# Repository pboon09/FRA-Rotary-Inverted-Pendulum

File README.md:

# FRA421 Embedded Systems Final Project

## Overview

Advanced embedded system implementation with state estimation filters, multiple interfaces, and safety-critical design for Rotary Inverted Pendulum control.

## Features

### State Estimation
- ✅ **Kalman Filter** - Optimal velocity estimation from encoder positions
- ✅ **Low-Pass Filter** - Noise reduction
- ✅ **CMSIS DSP Library** - Optimized signal processing

### Multi-Interface System
- ✅ **Colors Shield LED (8×8)** - End-effector position visualization
- ✅ **LCD Display** - Real-time joint position and velocity display
- ✅ **SD Card Logging** - Position/velocity data logging
- ✅ **Bluetooth (HC-05)** - Wireless command interface

### Safety & Efficiency
- ✅ **Safety-critical programming** - Fault detection, graceful degradation
- ✅ **Low Power Modes** - Sleep modes during idle periods
- ✅ **Watchdog Timer** - System reliability

### Hardware Integration
- ✅ **Custom PCB** - All interfaces integrated on single board
- ✅ **Non-blocking architecture** - Concurrent interface operation

## System Architecture
```
STM32 NUCLEO-G474RE
    ├─ Encoders (AMT103-V) → Kalman Filter → LQR Controller → Motor
    ├─ LED Matrix → End-effector position (X-Y grid)
    ├─ LCD → Position and velocity display
    ├─ SD Card → CSV data logging
    └─ Bluetooth → Command reception (start/stop/config)
```

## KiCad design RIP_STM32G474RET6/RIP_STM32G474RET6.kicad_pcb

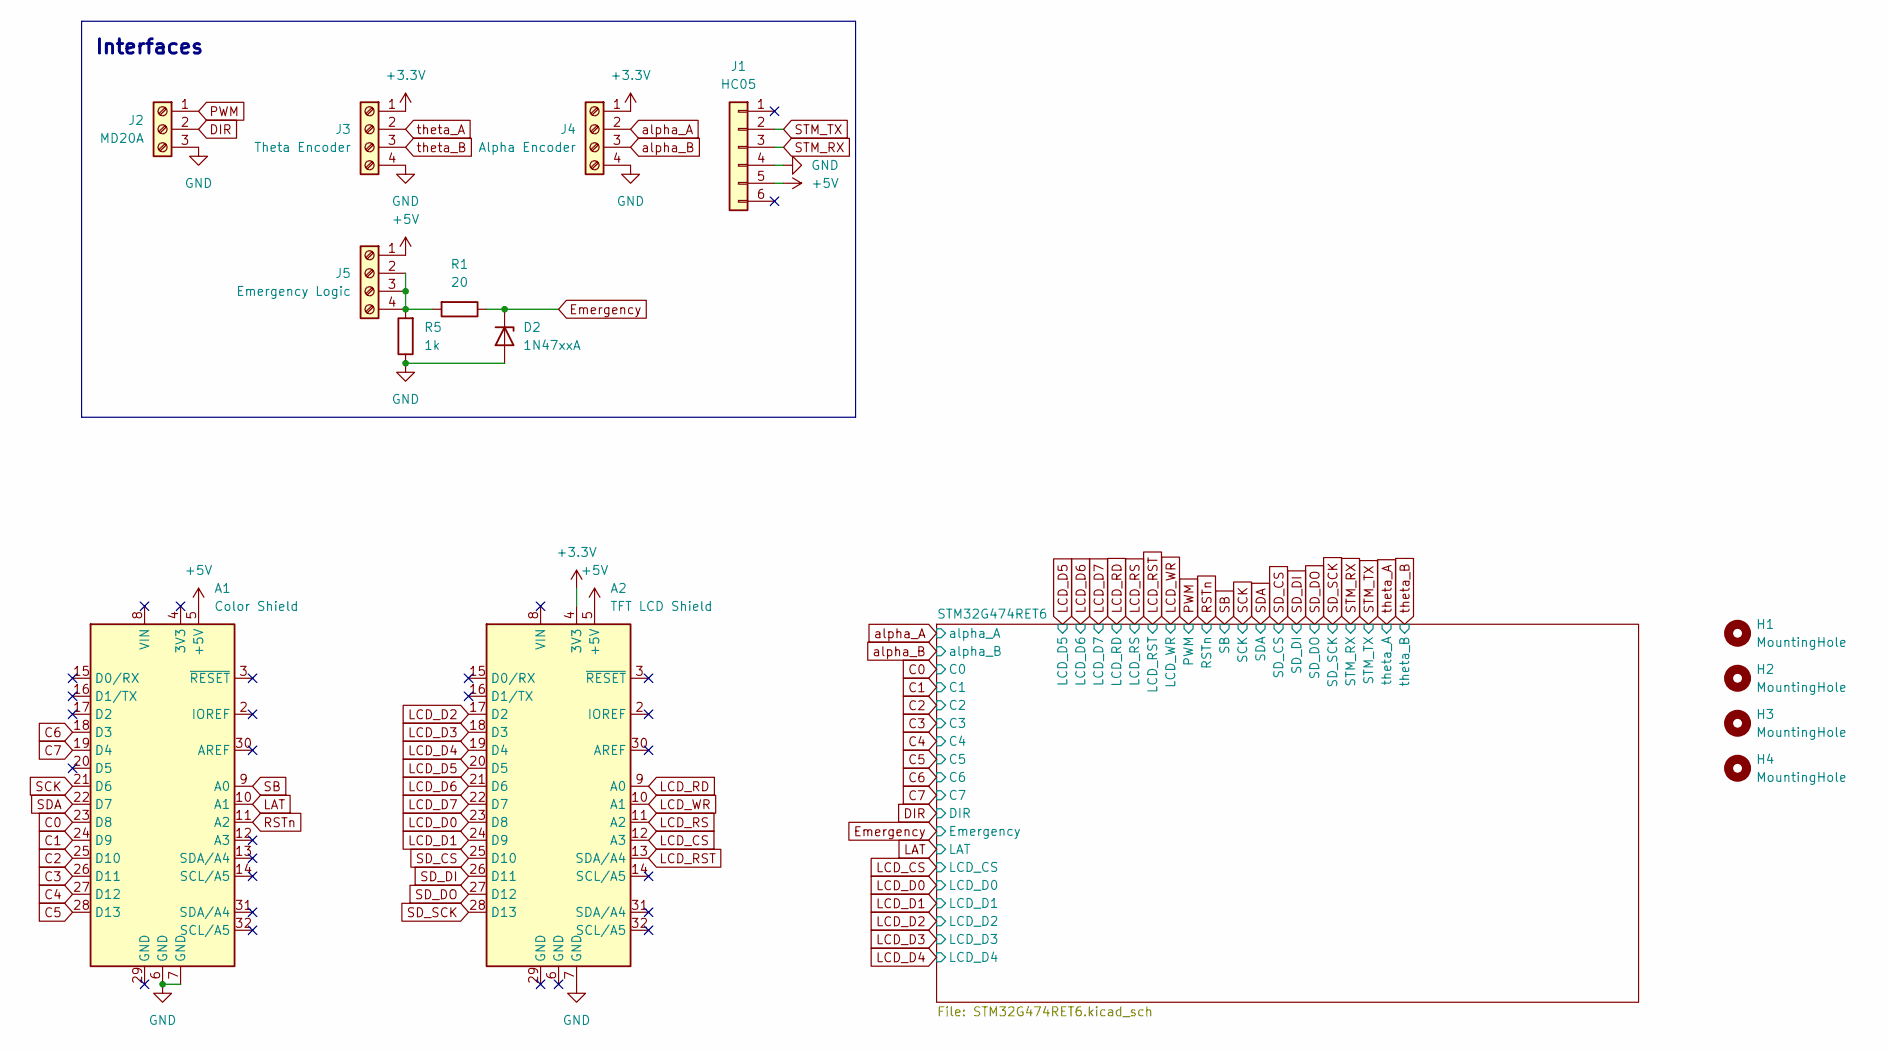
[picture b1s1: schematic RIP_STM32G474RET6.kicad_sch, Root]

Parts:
A1: Color Shield; Arduino_UNO_R3
A2: TFT LCD Shield; Arduino_UNO_R3
D2: 1N47xxA; D_DO-41_SOD81_P10.16mm_Horizontal
H1, H2, H3, H4: MountingHole; MountingHole_3mm
J1: HC05; PinSocket_1x06_P2.54mm_Vertical
J2: MD20A; PhoenixContact_MC_1,5_3-G-5.08_1x03_P5.08mm_Horizontal
J3: Theta Encoder; PhoenixContact_MC_1,5_4-G-5.08_1x04_P5.08mm_Horizontal
J4: Alpha Encoder; PhoenixContact_MC_1,5_4-G-5.08_1x04_P5.08mm_Horizontal
J5: Emergency Logic; PhoenixContact_MC_1,5_4-G-5.08_1x04_P5.08mm_Horizontal
R1: 20; R_Axial_DIN0309_L9.0mm_D3.2mm_P12.70mm_Horizontal
R5: 1k; R_Axial_DIN0309_L9.0mm_D3.2mm_P12.70mm_Horizontal

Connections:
+5V: A1.5 (+5V), A2.5 (+5V), J1.5, J5.1; also elsewhere on the board
C0: A1.23 (D8); also elsewhere on the board
C1: A1.24 (D9); also elsewhere on the board
C2: A1.25 (D10); also elsewhere on the board
C3: A1.26 (D11); also elsewhere on the board
C4: A1.27 (D12); also elsewhere on the board
C5: A1.28 (D13); also elsewhere on the board
C6: A1.18 (D3); also elsewhere on the board
C7: A1.19 (D4); also elsewhere on the board
DIR: J2.2; also elsewhere on the board
Emergency: D2.1 (K), R1.1; also elsewhere on the board
LAT: A1.10 (A1); also elsewhere on the board
LCD_CS: A2.12 (A3); also elsewhere on the board
LCD_D0: A2.23 (D8); also elsewhere on the board
LCD_D1: A2.24 (D9); also elsewhere on the board
LCD_D2: A2.17 (D2); also elsewhere on the board
LCD_D3: A2.18 (D3); also elsewhere on the board
LCD_D4: A2.19 (D4); also elsewhere on the board
LCD_D5: A2.20 (D5); also elsewhere on the board
LCD_D6: A2.21 (D6); also elsewhere on the board
LCD_D7: A2.22 (D7); also elsewhere on the board
LCD_RD: A2.9 (A0); also elsewhere on the board
LCD_RS: A2.11 (A2); also elsewhere on the board
LCD_RST: A2.13 (SDA/A4); also elsewhere on the board
LCD_WR: A2.10 (A1); also elsewhere on the board
unnamed: J5.2, J5.3, J5.4, R1.2, R5.2
PWM: J2.1; also elsewhere on the board
RSTn: A1.11 (A2); also elsewhere on the board
SB: A1.9 (A0); also elsewhere on the board
SCK: A1.21 (D6); also elsewhere on the board
SDA: A1.22 (D7); also elsewhere on the board
SD_CS: A2.25 (D10); also elsewhere on the board
SD_DI: A2.26 (D11); also elsewhere on the board
SD_DO: A2.27 (D12); also elsewhere on the board
SD_SCK: A2.28 (D13); also elsewhere on the board
STM_RX: J1.3; also elsewhere on the board
STM_TX: J1.2; also elsewhere on the board
VDD: A2.4 (3V3), J3.1, J4.1; also elsewhere on the board
VSSA: A1.6 (GND), A1.7 (GND), A2.7 (GND), D2.2 (A), J1.4, J2.3, J3.4, J4.4, R5.1; also elsewhere on the board
alpha_A: J4.2; also elsewhere on the board
alpha_B: J4.3; also elsewhere on the board
theta_A: J3.2; also elsewhere on the board
theta_B: J3.3; also elsewhere on the board

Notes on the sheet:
Interfaces

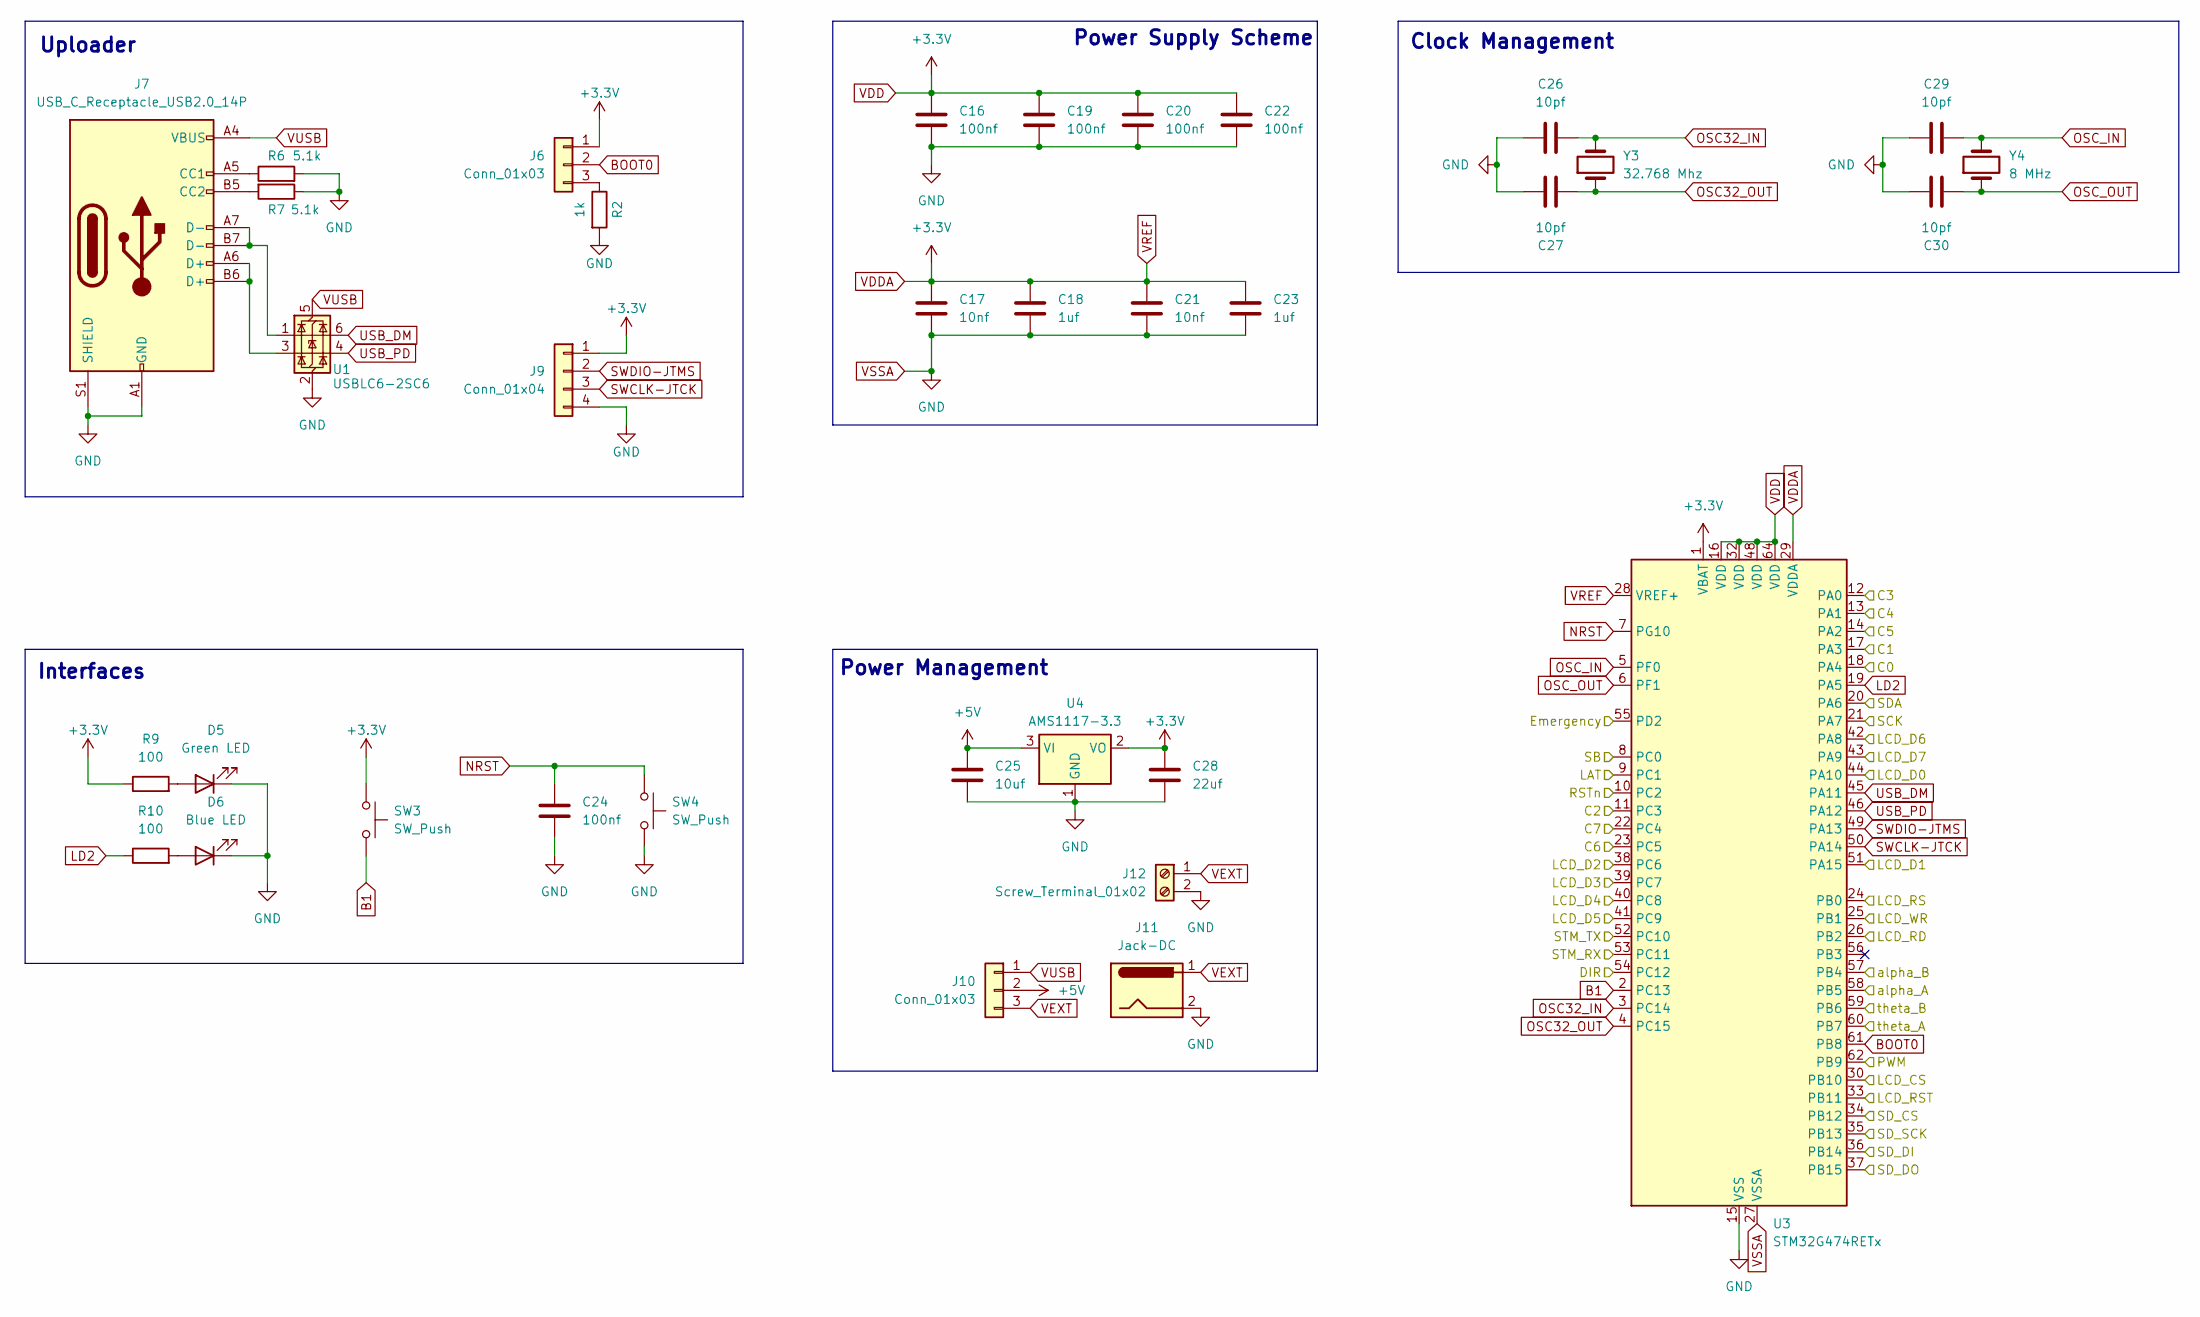
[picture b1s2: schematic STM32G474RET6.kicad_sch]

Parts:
C16, C19, C20, C22, C24: 100nf; C_0402_1005Metric
C17, C21: 10nf; C_0402_1005Metric
C18, C23: 1uf; C_0402_1005Metric
C25: 10uf; C_0402_1005Metric
C26, C27, C29, C30: 10pf; C_0402_1005Metric
C28: 22uf; C_0402_1005Metric
D5: Green LED; LED_0603_1608Metric
D6: Blue LED; LED_0603_1608Metric
J6, J10: Conn_01x03; PinHeader_1x03_P2.54mm_Vertical
J7: USB_C_Receptacle_USB2.0_14P; USB_C_Receptacle_GCT_USB4105-xx-A_16P_TopMnt_Horizontal
J9: Conn_01x04; PinHeader_1x04_P2.54mm_Vertical
J11: Jack-DC; BarrelJack_Horizontal
J12: Screw_Terminal_01x02; PhoenixContact_MC_1,5_2-G-5.08_1x02_P5.08mm_Horizontal
R2: 1k; R_0402_1005Metric
R6, R7: 5.1k; R_0402_1005Metric
R9, R10: 100; R_0402_1005Metric
SW3, SW4: SW_Push; SW_SPST_PTS810
U1: USBLC6-2SC6; SOT-23-6
U3: STM32G474RETx; LQFP-64_10x10mm_P0.5mm
U4: AMS1117-3.3; SOT-223-3_TabPin2
Y3: 32.768 Mhz; Crystal_SMD_MicroCrystal_CC7V-T1A-2Pin_3.2x1.5mm
Y4: 8 MHz; Crystal_SMD_MicroCrystal_CC7V-T1A-2Pin_3.2x1.5mm

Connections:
+5V: C25.1, J10.2, U4.3 (VI); also elsewhere on the board
B1: SW3.2, U3.2 (PC13)
BOOT0: J6.2, U3.61 (PB8)
C0: U3.18 (PA4); also elsewhere on the board
C1: U3.17 (PA3); also elsewhere on the board
C2: U3.11 (PC3); also elsewhere on the board
C3: U3.12 (PA0); also elsewhere on the board
C4: U3.13 (PA1); also elsewhere on the board
C5: U3.14 (PA2); also elsewhere on the board
C6: U3.23 (PC5); also elsewhere on the board
C7: U3.22 (PC4); also elsewhere on the board
DIR: U3.54 (PC12); also elsewhere on the board
Emergency: U3.55 (PD2); also elsewhere on the board
LAT: U3.9 (PC1); also elsewhere on the board
LCD_CS: U3.30 (PB10); also elsewhere on the board
LCD_D0: U3.44 (PA10); also elsewhere on the board
LCD_D1: U3.51 (PA15); also elsewhere on the board
LCD_D2: U3.38 (PC6); also elsewhere on the board
LCD_D3: U3.39 (PC7); also elsewhere on the board
LCD_D4: U3.40 (PC8); also elsewhere on the board
LCD_D5: U3.41 (PC9); also elsewhere on the board
LCD_D6: U3.42 (PA8); also elsewhere on the board
LCD_D7: U3.43 (PA9); also elsewhere on the board
LCD_RD: U3.26 (PB2); also elsewhere on the board
LCD_RS: U3.24 (PB0); also elsewhere on the board
LCD_RST: U3.33 (PB11); also elsewhere on the board
LCD_WR: U3.25 (PB1); also elsewhere on the board
LD2: R10.1, U3.19 (PA5)
NRST: C24.1, SW4.1, U3.7 (PG10)
unnamed: D5.2 (A), R9.2
unnamed: D6.2 (A), R10.2
unnamed: J6.3, R2.1
unnamed: J7.A5 (CC1), R6.1
unnamed: J7.B5 (CC2), R7.2
unnamed: J7.A6 (D+), J7.B6 (D+), U1.3 (I/O2)
unnamed: J7.A7 (D-), J7.B7 (D-), U1.1 (I/O1)
OSC32_IN: C26.1, U3.3 (PC14), Y3.2
OSC32_OUT: C27.2, U3.4 (PC15), Y3.1
OSC_IN: C29.1, U3.5 (PF0), Y4.2
OSC_OUT: C30.2, U3.6 (PF1), Y4.1
PWM: U3.62 (PB9); also elsewhere on the board
RSTn: U3.10 (PC2); also elsewhere on the board
SB: U3.8 (PC0); also elsewhere on the board
SCK: U3.21 (PA7); also elsewhere on the board
SDA: U3.20 (PA6); also elsewhere on the board
SD_CS: U3.34 (PB12); also elsewhere on the board
SD_DI: U3.36 (PB14); also elsewhere on the board
SD_DO: U3.37 (PB15); also elsewhere on the board
SD_SCK: U3.35 (PB13); also elsewhere on the board
STM_RX: U3.53 (PC11); also elsewhere on the board
STM_TX: U3.52 (PC10); also elsewhere on the board
SWCLK-JTCK: J9.3, U3.50 (PA14)
SWDIO-JTMS: J9.2, U3.49 (PA13)
USB_DM: U1.6 (I/O1), U3.45 (PA11)
USB_PD: U1.4 (I/O2), U3.46 (PA12)
VDD: C16.1, C17.1, C18.1, C19.1, C20.1, C21.1, C22.1, C23.1, C28.1, J6.1, J9.1, R9.1, SW3.1, U3.1 (VBAT), U3.16 (VDD), U3.28 (VREF+), U3.29 (VDDA), U3.32 (VDD), U3.48 (VDD), U3.64 (VDD), U4.2 (VO); also elsewhere on the board
VEXT: J10.3, J11.1, J12.1
VSSA: C16.2, C17.2, C18.2, C19.2, C20.2, C21.2, C22.2, C23.2, C24.2, C25.2, C26.2, C27.1, C28.2, C29.2, C30.1, D5.1 (K), D6.1 (K), J7.A1 (GND), J7.A12 (GND), J7.B1 (GND), J7.B12 (GND), J7.S1 (SHIELD), J9.4, J11.2, J12.2, R2.2, R6.2, R7.1, SW4.2, U1.2 (GND), U3.15 (VSS), U3.27 (VSSA), U3.31 (VSS), U3.47 (VSS), U3.63 (VSS), U4.1 (GND); also elsewhere on the board
VUSB: J7.A4 (VBUS), J7.A9 (VBUS), J7.B4 (VBUS), J7.B9 (VBUS), J10.1, U1.5 (VBUS)
alpha_A: U3.58 (PB5); also elsewhere on the board
alpha_B: U3.57 (PB4); also elsewhere on the board
theta_A: U3.60 (PB7); also elsewhere on the board
theta_B: U3.59 (PB6); also elsewhere on the board

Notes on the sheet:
Interfaces
Clock Management
Uploader
Power Management
Power Supply Scheme

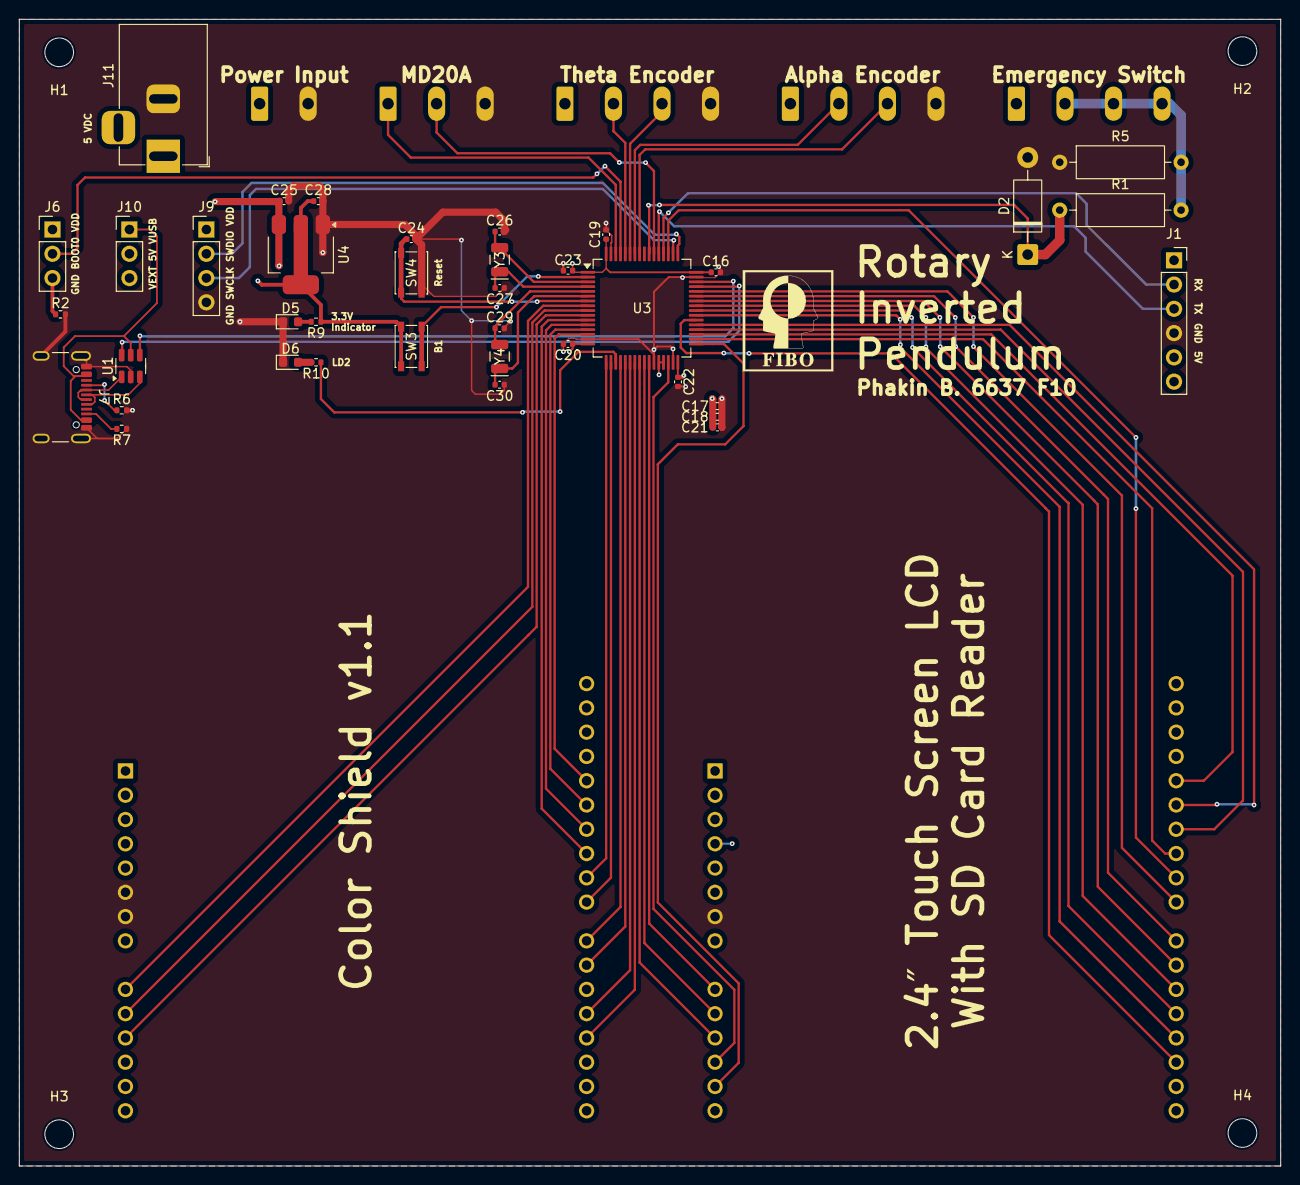
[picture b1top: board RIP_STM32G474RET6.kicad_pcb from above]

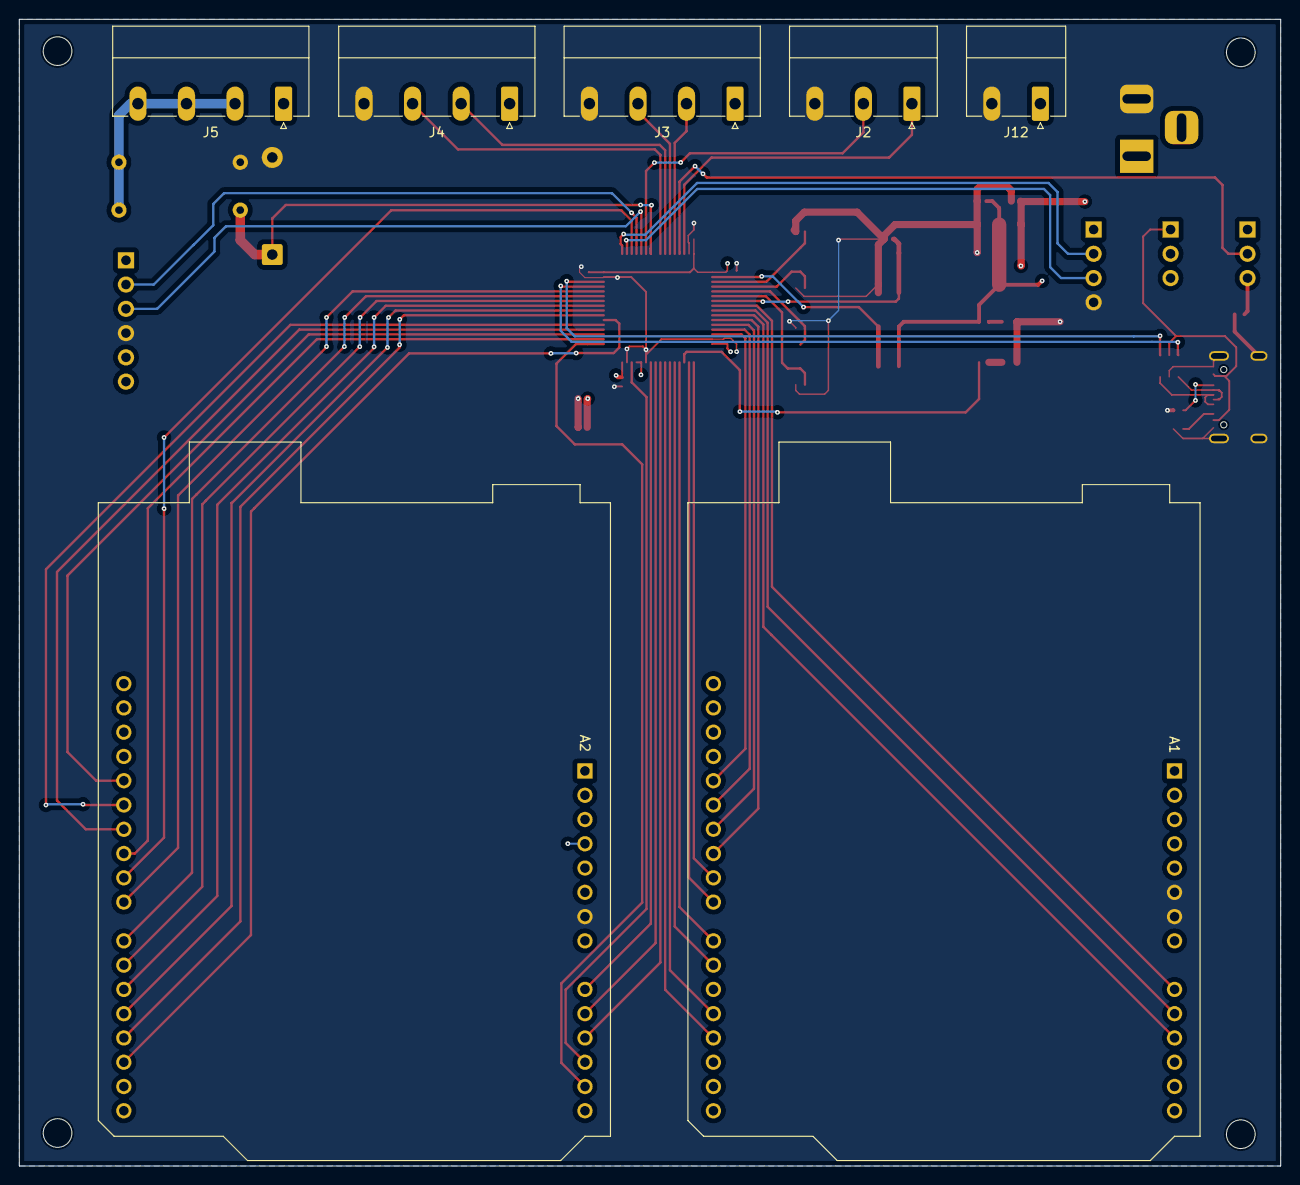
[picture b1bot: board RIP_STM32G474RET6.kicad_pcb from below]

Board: 4 copper layers, 132.0 x 120.0 mm, 49 parts (7 on the bottom side), 64 nets.

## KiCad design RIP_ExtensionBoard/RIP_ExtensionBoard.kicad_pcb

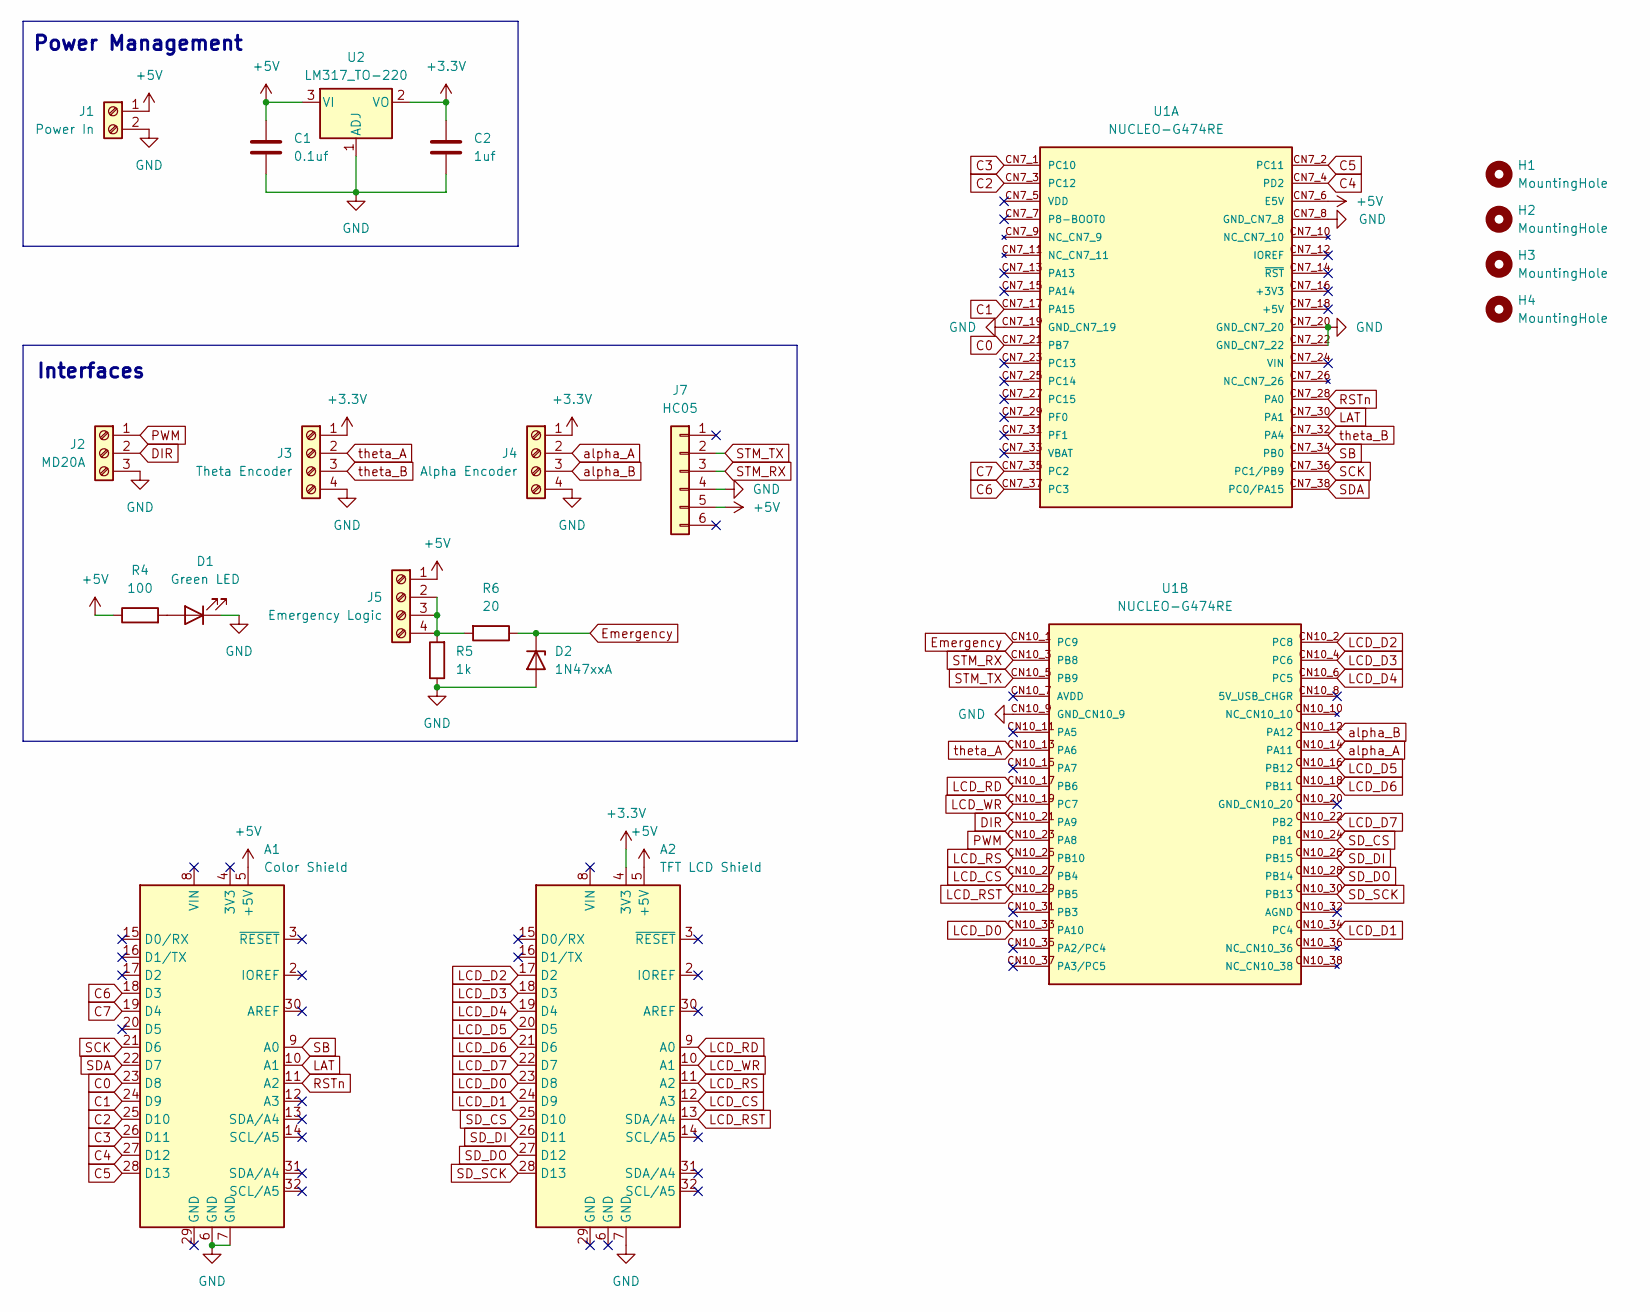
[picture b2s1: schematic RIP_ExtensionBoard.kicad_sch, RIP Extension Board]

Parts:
A1: Color Shield; Arduino_UNO_R3
A2: TFT LCD Shield; Arduino_UNO_R3
C1: 0.1uf; C_Disc_D5.0mm_W2.5mm_P2.50mm
C2: 1uf; C_Disc_D5.0mm_W2.5mm_P2.50mm
D1: Green LED; LED_D3.0mm
D2: 1N47xxA; D_DO-41_SOD81_P10.16mm_Horizontal
H1, H2, H3, H4: MountingHole; MountingHole_3mm
J1: Power In; PhoenixContact_MC_1,5_2-G-5.08_1x02_P5.08mm_Horizontal
J2: MD20A; PhoenixContact_MC_1,5_3-G-5.08_1x03_P5.08mm_Horizontal
J3: Theta Encoder; PhoenixContact_MC_1,5_4-G-5.08_1x04_P5.08mm_Horizontal
J4: Alpha Encoder; PhoenixContact_MC_1,5_4-G-5.08_1x04_P5.08mm_Horizontal
J5: Emergency Logic; PhoenixContact_MC_1,5_4-G-5.08_1x04_P5.08mm_Horizontal
J7: HC05; PinSocket_1x06_P2.54mm_Vertical
R4: 100; R_Axial_DIN0309_L9.0mm_D3.2mm_P12.70mm_Horizontal
R5: 1k; R_Axial_DIN0309_L9.0mm_D3.2mm_P12.70mm_Horizontal
R6: 20; R_Axial_DIN0309_L9.0mm_D3.2mm_P12.70mm_Horizontal
U1: NUCLEO-G474RE; MODULE_NUCLEO-G474RE; PARTREV 17
U2: LM317_TO-220; TO-220-3_Vertical

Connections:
+3.3V: A2.4 (3V3), C2.1, J3.1, J4.1, U2.2 (VO)
+5V: A1.5 (+5V), A2.5 (+5V), C1.1, J1.1, J5.1, J7.5, R4.1, U1.CN7_6 (E5V), U2.3 (VI)
C0: A1.23 (D8), U1.CN7_21 (PB7)
C1: A1.24 (D9), U1.CN7_17 (PA15)
C2: A1.25 (D10), U1.CN7_3 (PC12)
C3: A1.26 (D11), U1.CN7_1 (PC10)
C4: A1.27 (D12), U1.CN7_4 (PD2)
C5: A1.28 (D13), U1.CN7_2 (PC11)
C6: A1.18 (D3), U1.CN7_37 (PC3)
C7: A1.19 (D4), U1.CN7_35 (PC2)
DIR: J2.2, U1.CN10_21 (PA9)
Emergency: D2.1 (K), R6.1, U1.CN10_1 (PC9)
GND: A1.6 (GND), A1.7 (GND), A2.7 (GND), C1.2, C2.2, D1.1 (K), D2.2 (A), J1.2, J2.3, J3.4, J4.4, J7.4, R5.1, U1.CN7_8 (GND_CN7_8), U1.CN7_19 (GND_CN7_19), U1.CN7_20 (GND_CN7_20), U1.CN7_22 (GND_CN7_22), U1.CN10_9 (GND_CN10_9), U2.1 (ADJ)
LAT: A1.10 (A1), U1.CN7_30 (PA1)
LCD_CS: A2.12 (A3), U1.CN10_27 (PB4)
LCD_D0: A2.23 (D8), U1.CN10_33 (PA10)
LCD_D1: A2.24 (D9), U1.CN10_34 (PC4)
LCD_D2: A2.17 (D2), U1.CN10_2 (PC8)
LCD_D3: A2.18 (D3), U1.CN10_4 (PC6)
LCD_D4: A2.19 (D4), U1.CN10_6 (PC5)
LCD_D5: A2.20 (D5), U1.CN10_16 (PB12)
LCD_D6: A2.21 (D6), U1.CN10_18 (PB11)
LCD_D7: A2.22 (D7), U1.CN10_22 (PB2)
LCD_RD: A2.9 (A0), U1.CN10_17 (PB6)
LCD_RS: A2.11 (A2), U1.CN10_25 (PB10)
LCD_RST: A2.13 (SDA/A4), U1.CN10_29 (PB5)
LCD_WR: A2.10 (A1), U1.CN10_19 (PC7)
unnamed: D1.2 (A), R4.2
unnamed: J5.2, J5.3, J5.4, R5.2, R6.2
PWM: J2.1, U1.CN10_23 (PA8)
RSTn: A1.11 (A2), U1.CN7_28 (PA0)
SB: A1.9 (A0), U1.CN7_34 (PB0)
SCK: A1.21 (D6), U1.CN7_36 (PC1/PB9)
SDA: A1.22 (D7), U1.CN7_38 (PC0/PA15)
SD_CS: A2.25 (D10), U1.CN10_24 (PB1)
SD_DI: A2.26 (D11), U1.CN10_26 (PB15)
SD_DO: A2.27 (D12), U1.CN10_28 (PB14)
SD_SCK: A2.28 (D13), U1.CN10_30 (PB13)
STM_RX: J7.3, U1.CN10_3 (PB8)
STM_TX: J7.2, U1.CN10_5 (PB9)
alpha_A: J4.2, U1.CN10_14 (PA11)
alpha_B: J4.3, U1.CN10_12 (PA12)
theta_A: J3.2, U1.CN10_13 (PA6)
theta_B: J3.3, U1.CN7_32 (PA4)

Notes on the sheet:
Interfaces
Power Management

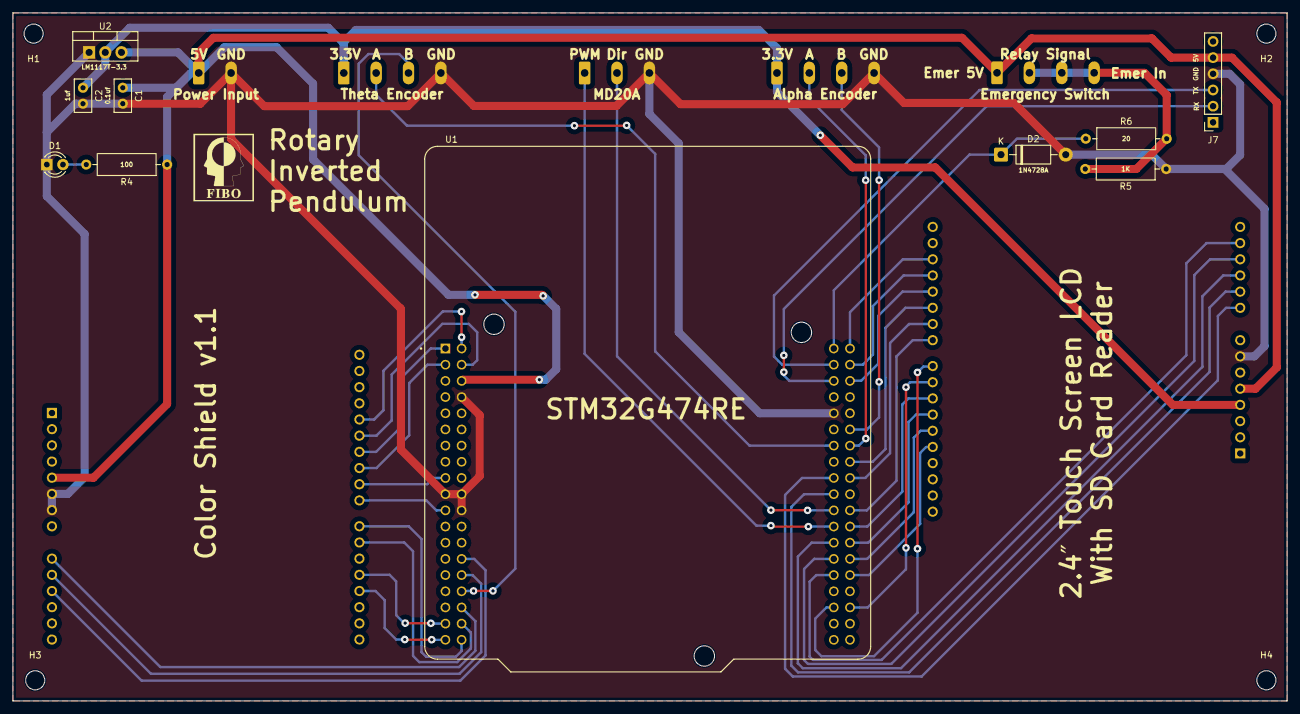
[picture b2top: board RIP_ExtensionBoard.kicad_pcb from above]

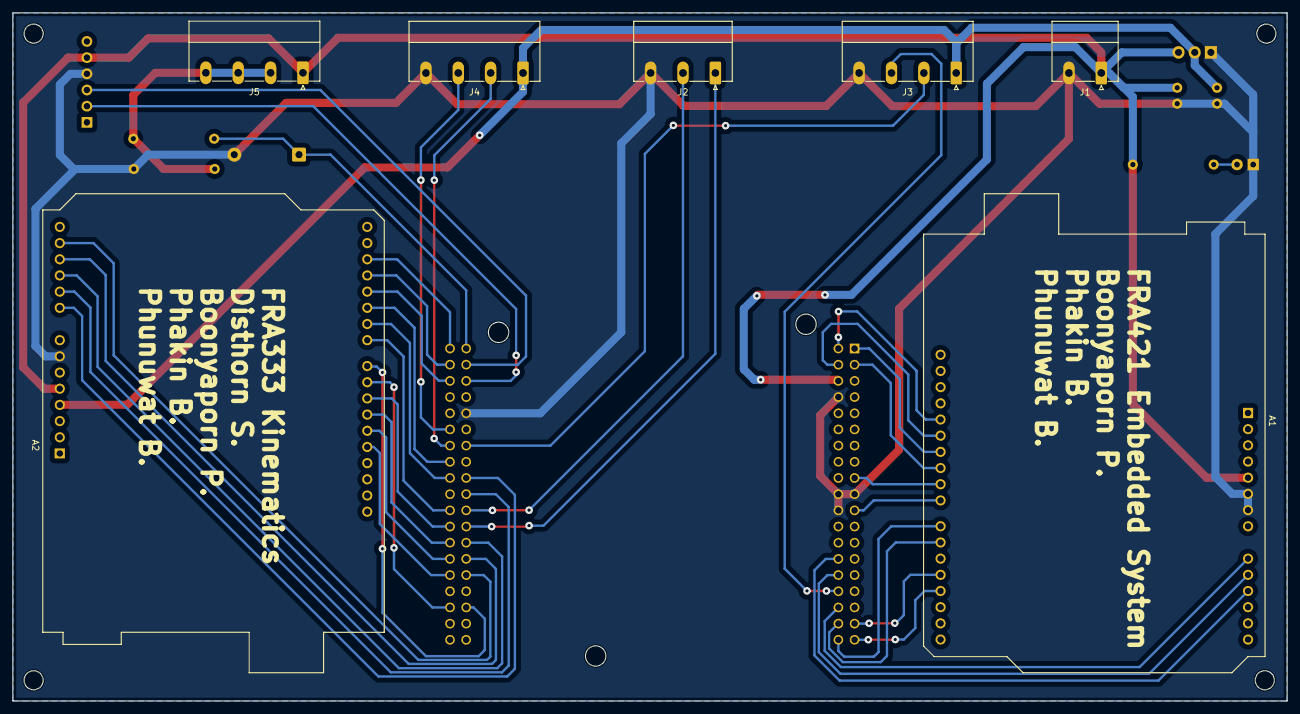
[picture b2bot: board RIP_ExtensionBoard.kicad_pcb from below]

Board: 2 copper layers, 200.0 x 108.0 mm, 21 parts (7 on the bottom side), 44 nets.

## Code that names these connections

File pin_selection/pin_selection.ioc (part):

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Mcu.Name=STM32G474R(B-C-E)Tx
Mcu.Package=LQFP64
Mcu.UserName=STM32G474RETx
PA0.GPIOParameters=GPIO_Label
PA0.GPIO_Label=RSTn
PA0.Signal=GPIO_Output
PA1.GPIOParameters=GPIO_Label
PA1.GPIO_Label=LAT
PA1.Signal=GPIO_Output
PA10.GPIOParameters=GPIO_Label
PA10.GPIO_Label=LCD_D0
PA10.Signal=GPIO_Output
PA11.Signal=S_TIM4_CH1
PA12.Signal=S_TIM4_CH2
PA13.GPIOParameters=GPIO_Label
PA13.GPIO_Label=T_SWDIO
PA13.Signal=SYS_JTMS-SWDIO
PA14.GPIOParameters=GPIO_Label
PA14.GPIO_Label=T_SWCLK
PA14.Signal=SYS_JTCK-SWCLK
PA15.GPIOParameters=GPIO_Label
PA15.GPIO_Label=C1
PA15.Signal=GPIO_Output
PA2.GPIOParameters=GPIO_Label
PA2.GPIO_Label=LPUART1_TX [STLINKV3E_VCP_RX]
PA2.Signal=LPUART1_TX
PA3.GPIOParameters=GPIO_Label
PA3.GPIO_Label=LPUART1_RX [STLINKV3E_VCP_TX]
PA3.Signal=LPUART1_RX
PA4.Signal=S_TIM3_CH2
PA5.GPIOParameters=GPIO_Label
PA5.GPIO_Label=LD2 [green led]
PA5.Signal=GPIO_Output
PA6.Signal=S_TIM3_CH1
PA8.Signal=S_TIM1_CH1
PA9.Signal=GPIO_Output
PB0.GPIOParameters=GPIO_Label
PB0.GPIO_Label=SB
PB0.Signal=GPIO_Output
PB1.GPIOParameters=GPIO_Label
PB1.GPIO_Label=SD_CS
PB1.Signal=GPIO_Output
PB10.GPIOParameters=GPIO_Label
PB10.GPIO_Label=LCD_RS
PB10.Signal=GPIO_Output
PB11.GPIOParameters=GPIO_Label
PB11.GPIO_Label=LCD_D6
PB11.Signal=GPIO_Output
PB12.GPIOParameters=GPIO_Label
PB12.GPIO_Label=LCD_D5
PB12.Signal=GPIO_Output
PB13.Mode=Full_Duplex_Master
PB13.Signal=SPI2_SCK
PB14.Mode=Full_Duplex_Master
PB14.Signal=SPI2_MISO
PB15.Mode=Full_Duplex_Master
PB15.Signal=SPI2_MOSI
PB2.GPIOParameters=GPIO_Label
PB2.GPIO_Label=LCD_D7
PB2.Signal=GPIO_Output
PB3.GPIOParameters=GPIO_Label
PB3.GPIO_Label=T_SWO
PB3.Signal=SYS_JTDO-SWO
PB4.GPIOParameters=GPIO_Label
PB4.GPIO_Label=LCD_CS
PB4.Signal=GPIO_Output
PB5.GPIOParameters=GPIO_Label
PB5.GPIO_Label=LCD_RST
PB5.Signal=GPIO_Output
PB6.GPIOParameters=GPIO_Label
PB6.GPIO_Label=LCD_RD
PB6.Signal=GPIO_Output
PB7.GPIOParameters=GPIO_Label
PB7.GPIO_Label=C0
PB7.Signal=GPIO_Output
PB8-BOOT0.Mode=Asynchronous
PB8-BOOT0.Signal=USART3_RX
PB9.Mode=Asynchronous
PB9.Signal=USART3_TX
PC0.GPIOParameters=GPIO_Label
PC0.GPIO_Label=SDA
PC0.Signal=GPIO_Output
PC1.GPIOParameters=GPIO_Label
PC1.GPIO_Label=SCK
PC1.Signal=GPIO_Output
PC10.GPIOParameters=GPIO_Label
PC10.GPIO_Label=C3
PC10.Signal=GPIO_Output
PC11.GPIOParameters=GPIO_Label
PC11.GPIO_Label=C5
PC11.Signal=GPIO_Output
PC12.GPIOParameters=GPIO_Label
PC12.GPIO_Label=C2
PC12.Signal=GPIO_Output
PC13.GPIOParameters=GPIO_Label
PC13.GPIO_Label=B1 [blue push button]
PC13.Signal=GPXTI13
PC14-OSC32_IN.GPIOParameters=GPIO_Label
PC14-OSC32_IN.GPIO_Label=RCC_OSC32_IN
PC14-OSC32_IN.Signal=RCC_OSC32_IN
PC15-OSC32_OUT.GPIOParameters=GPIO_Label
PC15-OSC32_OUT.GPIO_Label=RCC_OSC32_OUT
PC15-OSC32_OUT.Signal=RCC_OSC32_OUT
PC2.GPIOParameters=GPIO_Label
PC2.GPIO_Label=C7
PC2.Signal=GPIO_Output
PC3.GPIOParameters=GPIO_Label
PC3.GPIO_Label=C6
PC3.Signal=GPIO_Output
PC4.GPIOParameters=GPIO_Label
PC4.GPIO_Label=LCD_D1
PC4.Signal=GPIO_Output
PC5.GPIOParameters=GPIO_Label
PC5.GPIO_Label=LCD_D4
PC5.Signal=GPIO_Output
PC6.GPIOParameters=GPIO_Label
PC6.GPIO_Label=LCD_D3
PC6.Signal=GPIO_Output
PC7.GPIOParameters=GPIO_Label
PC7.GPIO_Label=LCD_WR
PC7.Signal=GPIO_Output
PC8.GPIOParameters=GPIO_Label
PC8.GPIO_Label=LCD_D2
PC8.Signal=GPIO_Output
PC9.GPIOParameters=GPIO_Label
PC9.GPIO_Label=Emergency
PC9.Signal=GPIO_Output
PD2.GPIOParameters=GPIO_Label
PD2.GPIO_Label=C4
PD2.Signal=GPIO_Output
PF0-OSC_IN.GPIOParameters=GPIO_Label
PF0-OSC_IN.GPIO_Label=RCC_OSC_IN
PF0-OSC_IN.Signal=RCC_OSC_IN
PF1-OSC_OUT.GPIOParameters=GPIO_Label
PF1-OSC_OUT.GPIO_Label=RCC_OSC_OUT
PF1-OSC_OUT.Signal=RCC_OSC_OUT
RCC.HSE_VALUE=24000000
RCC.SYSCLKFreq_VALUE=170000000
RCC.SYSCLKSource=RCC_SYSCLKSOURCE_PLLCLK
board=NUCLEO-G474RE
boardIOC=true

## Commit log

2025-10-20 init project
2025-11-02 stabilize v1
2025-11-02 rewrite
2025-11-02 More stabilize
2025-11-03 More stable
2025-11-03 add emergency state
2025-11-06 add matlab script
2025-11-06 PCB v1
2025-11-06 initial
2025-11-06 setup
2025-11-06 praying ja
2025-11-06 fix footprint
2025-11-06 export gerber
2025-11-06 correct model
2025-11-09 example
2025-11-11 rewiring
2025-11-12 for urdf
2025-11-12 display
2025-11-13 add js_raw tf
2025-11-16 fixed tf
2025-11-16 added marker array
2025-11-16 complete
2025-11-17 chip
2025-11-17 update2
2025-11-19 final
2025-11-20 change emergency pin
2025-11-29 controller with sd card
2025-12-05 integration
2025-12-10 update all
2025-12-10 update doc and readme
2025-12-16 all integration
2025-12-21 remove unusable
